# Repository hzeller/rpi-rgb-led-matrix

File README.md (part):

Controlling RGB LED display with Raspberry Pi GPIO
==================================================

A library to control commonly available 128x64, 64x64, 32x32 or 16x32 RGB LED panels
with the Raspberry Pi. Can support PWM up to 11Bit per channel, providing
true 24bpp color with CIE1931 profile.

Supports 3 chains with many panels each on a regular Pi.
On a Raspberry Pi 2 or 3, you can easily chain 12 panels in that chain
(so 36 panels total), but you can theoretically stretch that to up
to 96-ish panels (32 chain length) and still reach
around 100Hz refresh rate with full 24Bit color (theoretical - never tested
this; there might likely be timing problems with the panels that will creep
up then).

With fewer colors or so-called 'outdoor panels' you can control even more,
faster.

The LED-matrix library is (c) Henner Zeller <h.zeller@acm.org>, licensed with
[GNU General Public License Version 2.0 (or any later version)](http://www.gnu.org/licenses/gpl-2.0.txt)
(which means, if you use it in a product somewhere, you need to make the
source and all your modifications available to the receiver of such product so
that they have the freedom to adapt and improve).
Yes, you are also allowed to use
this code under the [GNU General Public License Version 3.0](http://www.gnu.org/licenses/gpl-3.0.txt)
which allows linking with Apache 2.0 code and LGPL-3.0 code.

## Discourse discussion group

**If you'd like help, please do not file a bug, use the discussion board instead:**
https://rpi-rgb-led-matrix.discourse.group/  (obviously please read this whole page first).
If you file a bug asking for personal help instead of using the discourse group, please
state in your bug that you have read this entire page and that you're indeed filing a bug
or request for improvement. Otherwise, please use the discourse group.

Overview
--------
The RGB LED matrix panels can be scored at [Sparkfun][sparkfun],
[AdaFruit][ada] or eBay and Aliexpress. If you are in China, I'd try to get
them directly from some manufacturer, Taobao or Alibaba.

The `RGBMatrix` class provided in `include/led-matrix.h` does what is needed
to control these. You can use this as a library in your own projects or just
use the demo binary provided here which provides some useful examples.

Check out [utils/ directory for some ready-made tools](./utils) to get started
using the library, or the [examples-api-use/](./examples-api-use) directory if
you want to get started programming your own utils.

Panels supported
----------------
This library does not support PWM panels (which actually are better, but need
a completely different driver).\
It should support most other panels with direct addressing (3 to 5 address lines,
ABC for 8x2=16 lines, ABCD for 16x2=32 lines, and ABCDE for 32x2=64 lines).
It also supports panels using shift registers for line addressing, also called ABC
panels up to 64 lines.\
However some amount of panels have uncommon pixel layouts, especially the brighter
panels and may require special pixel mappers (some are called zigzag or zagzig, see
https://rpi-rgb-led-matrix.discourse.group/t/p10rgb-3535-4s-zaggiz-1-4scan-abc-p10-panels-and-https-github-com-2dom-pxmatrix/921 )

Until this wiki has its own confirmed list of working panels, you can refer to
this list: https://github.com/board707/DMD_STM32/wiki/Led_drivers and assume
that all supported panels there should work with this library, or could work
with minimal work to create a pixel mapper.
Please do refer to --led-multiplexing=<0..17> mentioned below and try all values. \
2025/11 update: DMD_STM32 has started adding experimental support for some PWM panels.
These should be labelled as "special" in the table above. They are not supported by this
lib, as it only supports non PWM panels (until someone contributes PWM support).

PWM/E-PWM/S-PWM Panels
----------------------
Newer PWM panels are not currently supported by this lib, but support would really be appreciated.
- https://github.com/hzeller/rpi-rgb-led-matrix/issues/466 - Master bug tracking PWM efforts
- https://github.com/hzeller/rpi-rgb-led-matrix/issues/1866 - Continued discussion

Some experimentation and success has been made with the following fork. Some panel support with FM6373, FM6363, SM16380SH
- https://github.com/kingdo9/rpi-rgb-led-matrix_pwm_experiment

Raspberry Pi 1-5 supported
------------------------------
This library supports the old Raspberry Pi's Version 1 with 26 pin header and
also the B+ models, the Pi Zero, Raspberry Pi 2,3,4 and 5 with 40 pins, as well
as the Compute Modules which have 44 GPIOs.

#### Raspberry Pi 5 support has now been added.
There are two modes to run this on the Pi 5 

**--led-rp1-rio=0** - Uses the Pi 5 coprocessor RP1 to perform the work (default) - Very minimal CPU usage

**--led-rp1-rio=1** - Uses Registered IO block of RP1 to communicate with the GPIO - Higher CPU usage but much faster performance.\
**NOTE: --led-slowdown-gpio** can have the opposite effect in this mode, so going from 2 to 3 may increase performance slightly with --led-rp1-rio=1.

Pi 5 Discussion -  https://github.com/hzeller/rpi-rgb-led-matrix/issues/1603

Thanks to contributions from the following libraries to help implement this.
https://github.com/adafruit/Adafruit_Blinka_Raspberry_Pi5_Piomatter \
https://github.com/bitslip6/rpi-gpu-hub75-matrix \
https://www.i-programmer.info/programming/148-hardware/16887-raspberry-pi-iot-in-c-pi-5-memory-mapped-gpio.html

The 26 pin models can drive one chain of RGB panels, the 40 pin models
**up to three** chains in parallel (each chain 12 or more panels long).
The Compute Module can drive **up to 6 chains in parallel**.
The Raspberry Pi 2 and 3 are faster and generally preferred to the older
models (and the Pi Zero). With the faster models, the panels sometimes
can't keep up with the speed; check out
this [troubleshooting section](#troubleshooting) what to do.

A lightweight, non-GUI, distribution such as [DietPi] is recommended.
[Raspbian Lite][raspbian-lite] is a bit easier to get started with and
is a good second choice.

Types of Displays
-----------------
There are various types of displays that come all with the same Hub75 connector.
They vary in the way the multiplexing is happening so this library supports
options to choose that.
All these are configured by flags (or, programmatically, in an [Options struct](include/led-matrix.h#L57)).

If you have a 64x32 display, you need to supply the flags
`--led-cols=64 --led-rows=32` for instance.

Depending on the Matrix, there are various configuration options that
you might need to set for it to work. See further below in the README for the
[detailed description of these](#changing-parameters-via-command-line-flags).
While the `--led-rows` and `--led-cols` can be derived from simply looking
at the panels, the other options might require some experimenting to find the
right setting if there is no description provided by the manufacturer of
the panel. Going through these options for experiments would typically not do
harm, so you're free to experiment to find your setting.

Flag                                | Description
:---------------      | :-----------------
`--led-cols`          | Columns in the LED matrix, the 'width'.
`--led-rows`          | Rows in the LED matrix, the 'height'.
`--led-multiplexing`  | In particular bright outdoor panels with small multiplex ratios require this. Often an indicator: if there are fewer address lines than expected: ABC (instead of ABCD) for 32 high panels and ABCD (instead of ABCDE) for 64 high panels.
`--led-row-addr-type` | Addressing of rows; in particular panels with only AB address lines might indicate that this is needed.
`--led-panel-type`    | Chipset of the panel. In particular if it doesn't light up at all, you might need to play with this option because it indicates that the panel requires a particular initialization sequence.

Panels can be chained by connecting the output of one panel to the input of
the next panel. You can chain quite a few together, but the refresh rate will
reduce with longer chains.

The 64x64 matrixes typically come in two kinds: with 5 address
lines (A, B, C, D, E), or (A, B); the latter needs a `--led-row-addr-type=1`
parameter. So-called 'outdoor panels' are typically brighter and allow for
faster refresh-rate for the same size, but do some multiplexing internally
of which there are a few types out there; they can be chosen with
the `--led-multiplexing` parameter.
Many 128x64 panels now use ABC addressing using shift registers, instead of direct
ABCDE addressing. Look at using --led-row-addr-type=5 or --led-row-addr-type=3
with them (and you may need to use --led-slowdown-gpio of 2 or more. Please
see this bug for more details: https://github.com/hzeller/rpi-rgb-led-matrix/issues/1774

There are some panels that have a different chip-set than the default HUB75.
These require some initialization sequence. The current supported types are
`--led-panel-type=FM6126A` and `--led-panel-type=FM6127`.

Generally, the higher scan-rate (e.g. 1:8), a.k.a. outdoor panels generally
allow faster refresh rate, but you might need to figure out the multiplexing
mapping if one of the three provided does not work.

Some 32x16 outdoor matrixes with 1:4 scan (e.g. [Qiangli Q10(1/4) or X10(1/4)](http://qiangliled.com/products-63.html))
have 4 address line (A, B, C, D). For such matrices is necessary to
use `--led-row-addr-type=2` parameter. Also the matrix Qiangli Q10(1/4)
have "Z"-stripe pixel mapping and in this case, you'd use two parameters
at the same time `--led-row-addr-type=2 --led-multiplexing=4`.

Sub-Pages
---------
This documentation is split into parts that help you through the process

- 
    [**Wire up the matrix to your Pi**](./wiring.md). This document describes
    what goes where.
- [How to map pixels between panels or within panels](./lib). This is crucial for figuring out pixel mappers,
  matrix mappers and so forth. This is where you will learn about panel layout with U-Mapper, V-Mapper, V-Mapper:Z
- [Adapter GPIO boards output to up to 3 channels (electrodragon board recommended)](./adapter).
    If you have an [Adafruit HAT] or [Adafruit Bonnet], you can choose that with
    a command line option [described below](#if-you-have-an-adafruit-hat-or-bonnet)
- [All the command line options you can give to demo and in turn use in your library code](./examples-api-use).
- [Installing an Optimized Kernel to fix most flickering issues](./optimized-kernel)

Python Support
--------------
The python bindings have been overhauled as of February 2026 and are now built with scikit-build-core and cmake. While
this update has been tested there are likely edge cases that have not been caught. Please subscribe to the master Python
bug to assist or check for the latest updates.
https://github.com/hzeller/rpi-rgb-led-matrix/issues/1749.

The entire repository itself is PIP-able and can be installed as a package directly. Python dev packages are required.
```
sudo apt-get install python-dev-is-python3 python3-pil cython3
pip install git+https://github.com/hzeller/rpi-rgb-led-matrix
```

Rpi Hardware Support
--------------------
While this code should still work on rPi1 or Rpi0, those are underpowered and not recommended. An ESP32 is cheaper and faster.
Rpi2 is honestly old and slow too.
Rpi3 / Rpi3a / Rpi0 2wl will work for most displays but will be slow if you are rotating a huge display in a mapper (Rpi0 2wl is a slightly faster version of Rpi3)
Rpi4 is the fastest supported chip which will need a higher slowdown gpio value to avoid overwhelming panels (if they display garbage)
Rpi5 is not officially supported as of 2025/11, but see https://github.com/hzeller/rpi-rgb-led-matrix/issues/1603

Let's do it
------------
  1. Run a demo. You find that in the
     [examples-api-use/](./examples-api-use#running-some-demos) directory:
```
make -C examples-api-use
sudo examples-api-use/demo -D0
```
  2. Use the utilities. The [utils](./utils) directory has some ready-made
    useful utilities to show content. [Go there](./utils) to see how to
    compile and run these.
  3. Write your own programs using the Matrix in C++ or one of the
     bindings such as Python or C#.

### Wiring / Boards

Please see the [Adadpter Boards or Self Wiring](./adapter).

Summary is:
- Yes you can self wire without level shifters and it will work most of the time, but if you're not in a hurry get a board
- https://www.electrodragon.com/product/rgb-matrix-panel-drive-board-for-raspberry-pi-v2/ **is the recommended solution with 3 channels and level shifters**. You can't go wrong there, but expect a bit of shipping time.
- If shipping time is crucial and you don't want to wire your own, Adafruit sells a single channel board (the electrodragon one is 3 channels), but note that its wiring is non standard and requires a special compile option or command line argument: https://www.adafruit.com/product/3211

### Utilities

The [utils directory](./utils) is meant for ready utilities to show images or
animated gifs or videos. Read the [README](./utils/README.md) there for
instructions how to compile.

There are external projects that use this library and provide higher level
network protocols, such as the
 * [FlaschenTaschen implementation](https://github.com/hzeller/flaschen-taschen)
   (VLC can send videos to it natively)
 * [PixelPusher implementation](https://github.com/hzeller/rpi-matrix-pixelpusher) (common in light art installations)
 * [ZeroMQ-server](https://github.com/Knifa/led-matrix-zmq-server) to receive
   content.
 * Marc's [FastLED_RPIRGBPanel_GFX](http://marc.merlins.org/perso/arduino/post_2020-01-01_Running-FastLED_-Adafruit_GFX_-and-LEDMatrix-code-on-High-Resolution-RGBPanels-with-a-Raspberry-Pi.html) allows running arduino code on linux/rPi and display on bigger RGBPanel matrices than arduino chips, can.

### API

The library comes as an API that you can use for your own utilities and use-cases.

  * The native library is a C++ library (see [include/](./include)).
    Example uses you find in the [examples-api-use/](./examples-api-use)
    directory.
  * If you prefer to program in C, there is also a
    [C API](./include/led-matrix-c.h).
  * In the [python](./bindings/python) subdirectory, you find a Python API including a
    couple of [examples](./bindings/python/samples) to get started.
  * There are a couple of external bindings, such as
      * [Nodejs binding] by Maxime Journaux
      * [Nodejs/Typescript binding] by Alex Eden
      * [Go binding] by Máximo Cuadros
      * [Rust binding] by Vincent Pasquier

### Changing parameters via command-line flags

For the programs in this distribution and also automatically in your own
programs using this library, there are a lot of parameters provided as command
line flags, so that you don't have to re-compile your programs to tweak them.
Some might need to be changed for your particular kind of panel.

Here is a little run-down of what these command-line flags do and when you'd
like to change them.

First things first: if you have a different wiring than described in
[wiring](./wiring.md), for instance if you have an Adafruit HAT/Bonnet, you can
choose these here:

```
--led-gpio-mapping=<gpio-mapping>: Name of GPIO mapping used. Default "regular"
```

This can have values such as
  - `--led-gpio-mapping=regular` The standard mapping of this library, described in the [wiring](./wiring.md) page.
  - `--led-gpio-mapping=adafruit-hat` The Adafruit HAT/Bonnet, that uses this library or
  - `--led-gpio-mapping=adafruit-hat-pwm` Adafruit HAT with the anti- hardware mod [described below](#improving-flicker-hardware-patch).
  - `--led-gpio-mapping=compute-module` Additional 3 parallel chains can be used with the Compute Module.

Learn more about the mappings in the [wiring documentation](wiring.md#alternative-hardware-mappings).

#### GPIO speed

```
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
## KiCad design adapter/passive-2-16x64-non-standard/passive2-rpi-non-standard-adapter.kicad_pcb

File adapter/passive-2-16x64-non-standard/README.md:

Adapter PCB to support up to 2 panel chains
===========================================

   * This adapter is designed specifically for 16x64 LED matrix boards that use a non standard pin layout
 
   * This is a passive board. It is simple, but the logic level will be out of
     spec for the LED matrix (3.3V vs. 5V) which might or might not work.
     Driving long cables with the GPIO pins is also not a good idea.
   * Only really advisable, if the LED panels have 74HCT245 (as opposed to just
     74HC245) in their input stage, because then they can deal properly with
     the 3.3V logic levels coming from the Pi.
   * Open source KiCAD PCB EDA format.
   * autorouted 
   * The FAB files are provided as [passive2-rpi-non-standard-adapter-fab.zip](./passive2-rpi-non-standard-adapter-fab.zip)

This board is [shared on OSH Park][osh-passive3] (not affiliated).

![Preview][rendering]

[rendering]: ../../img/passive2-rpi-non-standard-adapter.png

[osh-passive3]: https://oshpark.com/shared_projects/LxM7tyyO

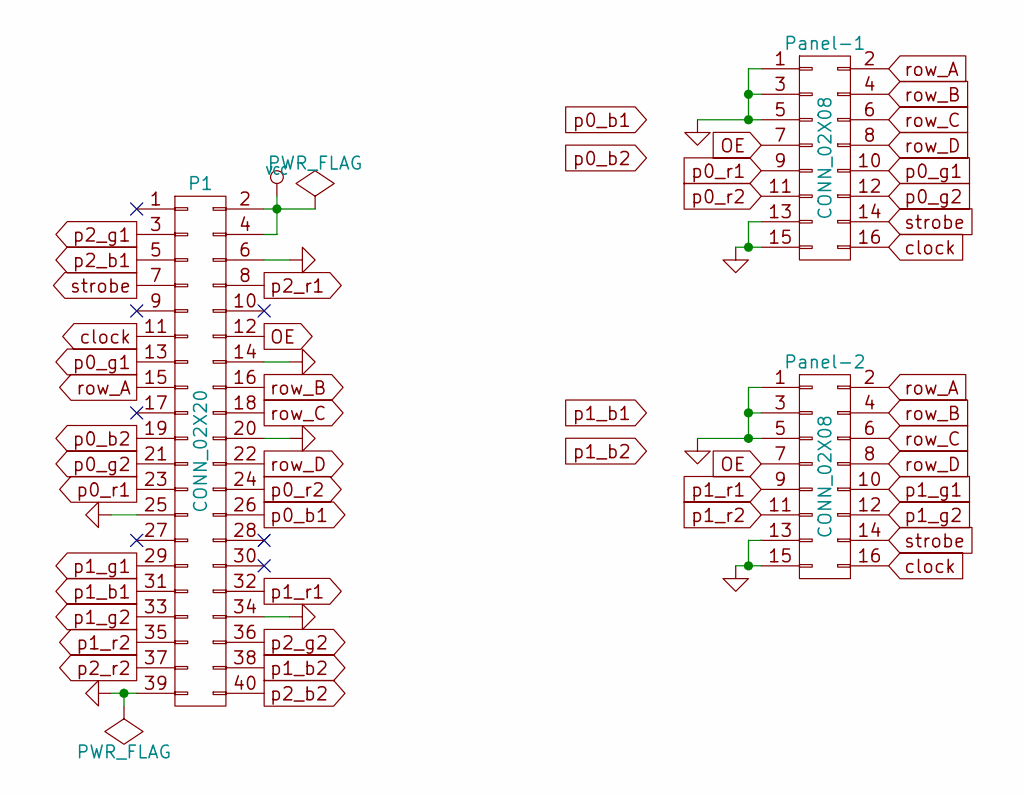
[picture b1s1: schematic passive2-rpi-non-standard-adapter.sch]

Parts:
P1: CONN_02X20; Pin_Header_Straight_2x20
Panel-1, Panel-2: CONN_02X08; Pin_Header_Straight_2x08

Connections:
GND: P1.6, P1.14, P1.20, P1.25, P1.34, P1.39, Panel-1.1, Panel-1.3, Panel-1.5, Panel-1.13, Panel-1.15, Panel-2.1, Panel-2.3, Panel-2.5, Panel-2.13, Panel-2.15
OE: P1.12, Panel-1.7, Panel-2.7
VCC: P1.2, P1.4
clock: P1.11, Panel-1.16, Panel-2.16
p0_b1: P1.26
p0_b2: P1.19
p0_g1: P1.13, Panel-1.10
p0_g2: P1.21, Panel-1.12
p0_r1: P1.23, Panel-1.9
p0_r2: P1.24, Panel-1.11
p1_b1: P1.31
p1_b2: P1.38
p1_g1: P1.29, Panel-2.10
p1_g2: P1.33, Panel-2.12
p1_r1: P1.32, Panel-2.9
p1_r2: P1.35, Panel-2.11
p2_b1: P1.5
p2_b2: P1.40
p2_g1: P1.3
p2_g2: P1.36
p2_r1: P1.8
p2_r2: P1.37
row_A: P1.15, Panel-1.2, Panel-2.2
row_B: P1.16, Panel-1.4, Panel-2.4
row_C: P1.18, Panel-1.6, Panel-2.6
row_D: P1.22, Panel-1.8, Panel-2.8
strobe: P1.7, Panel-1.14, Panel-2.14

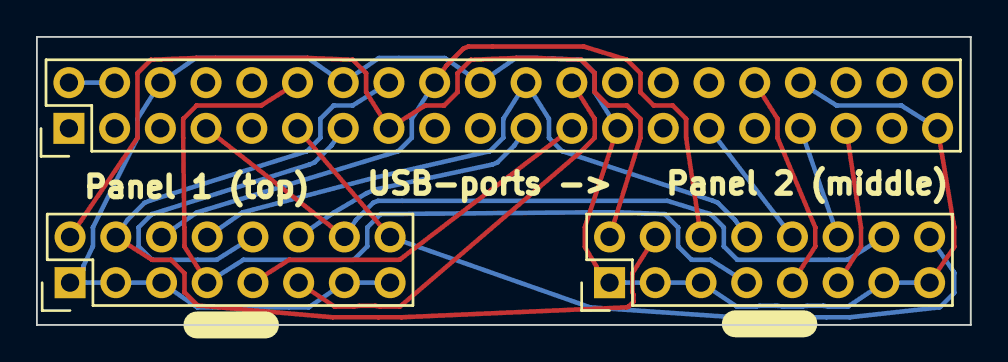
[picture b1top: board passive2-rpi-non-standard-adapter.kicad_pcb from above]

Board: 2 copper layers, 51.9 x 16.0 mm, 3 parts (0 on the bottom side), 17 nets.

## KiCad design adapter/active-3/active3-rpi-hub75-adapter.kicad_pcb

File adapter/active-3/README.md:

Adapter PCB to support up to 3 panel chains
===========================================

   * Supports up to three panel chains for newer plus models and
     Raspberry Pi 2 that have 40 GPIO pins.
   * Uses HCT245 to level shift signals from 3.3V to 5V and shield
     the Raspberry Pi GPIOs from overloading.
   * Open source KiCAD PCB EDA format.
   * Optional: Pads to power the Pi with 5V, including optional capacitor footprints.
   * Connector for RxD input (literally the only GPIO pin left) in case you want to
     make your panel controlled with a serial interface (3.3V logic level).
   * Provides a way to choose the pinout for different kinds of 64x64 matrixes.
   * (not very pretty layout, was just lazy and let the auto-router generate the first pass)
   * BOM:
     - 4x 74HCT245 or 74AHCT245 in 20-SOIC, 7.5mm package which should make
     it easy to hand-solder. Make sure to get the variant with the **T**: HC**T** or AHC**T**
     (there are also HC or AHC, don't use these).
     - 4x 100nF ceramic capacitor (0805 package)
     - 1x 10kOhm resistor (0805 package). Not critical, just a pullup (2.2k .. 15k probably ok).
     - 3x 16pin IDC (=2x8) male receptible to connect the panels.
     - 1x 40pin female connector to connect to the RPi.
     - 1x (optional) 22μF .. 100μF capacitor for 5V rail (either 1206 SMD or
       radial electrolytic with 2.5mm pitch/6.3mm diameter)
   * The Gerber FAB files are provided as [active3-rpi-hub75-adapter-fab.zip](./active3-rpi-hub75-adapter-fab.zip)

The board is also [shared on OSH Park][osh-active3] (not affiliated).

![Preview][rendering]
![Real World][real-world]

Essentially, this is connecting the output pins through level shifting buffers (they
are operated at 5V, but the HCT series chips accept 3.3V input levels from the Pi). The
strobe, OE and clock signals are separately buffered for each connector.

![Schematic][schematic]

## Optional

### Power in

The area on the left has 5V/GND input pads, that allow you to power your Raspberry Pi from
a 5V source ... which you are likely to have as you are powering the LED Matrix. This is often
more convenient than using the USB connector to power the Pi.

If you do that, there are pads to add a capacitor to smooth the supply - two footprints are
provided: C5 and C6 for through-hole or surface mount components. The value is not critical;
I usually use a 22μF/6.3V ceramic capacitor on the C6 pads.

### Choose E-Line for 64x64 panels with 1:32 multiplexing

If you have a 64x64 matrix with 1:32 multiplexing, you need to supply an `E`-address line to it.
While the Address lines `A` to `D` have fixed positions on the Hub75 connector, there
seem to be two different ways to connect the `E` address line: it is either on pin 4 or pin 8
of the connector. So this adapter board provides the flexibility to choose the right pin for
your matrix.

Look at the back of the matrix or the documentation to find out for your specific board where
to connect E.

Once you know that, the jumper area in the bottom left of this adapter board allows to choose
to which pin to connect the E-address line to. The corresponding other pin should be connected
to GND. Simply solder a wire bridge as indicated below (or use a jumper that you can change later).

If you are not using such 64x64 matrix, you can connect both these pins to GND.

Here are the typical configurations:

No 1:32 64x64: to GND    | E-Line on Pin 4   | E-Line on Pin 8|
-------------------------|-------------------|----------------
![][config-default]      |![][config-pin4]   |![][config-pin8]

### Input for serial RxD

If you are not using a 64x64 display that occupies the E-Line, you can use the RxD serial input -
this might come in handy if you are using the display to be controlled by a serial line. Be aware
that the input requires 3.3V level, so if you have a RS232, make sure to first adapt the levels.

[rendering]: ../../img/active3-pcb.png
[config-default]: ../../img/active3-pcb-config-default.png
[config-pin4]: ../../img/active3-pcb-config-pin4.png
[config-pin8]: ../../img/active3-pcb-config-pin8.png
[schematic]: ../../img/active3-schematic.png
[real-world]: ../../img/three-parallel-panels-soic.jpg
[osh-active3]: https://oshpark.com/shared_projects/6xAD1VXr

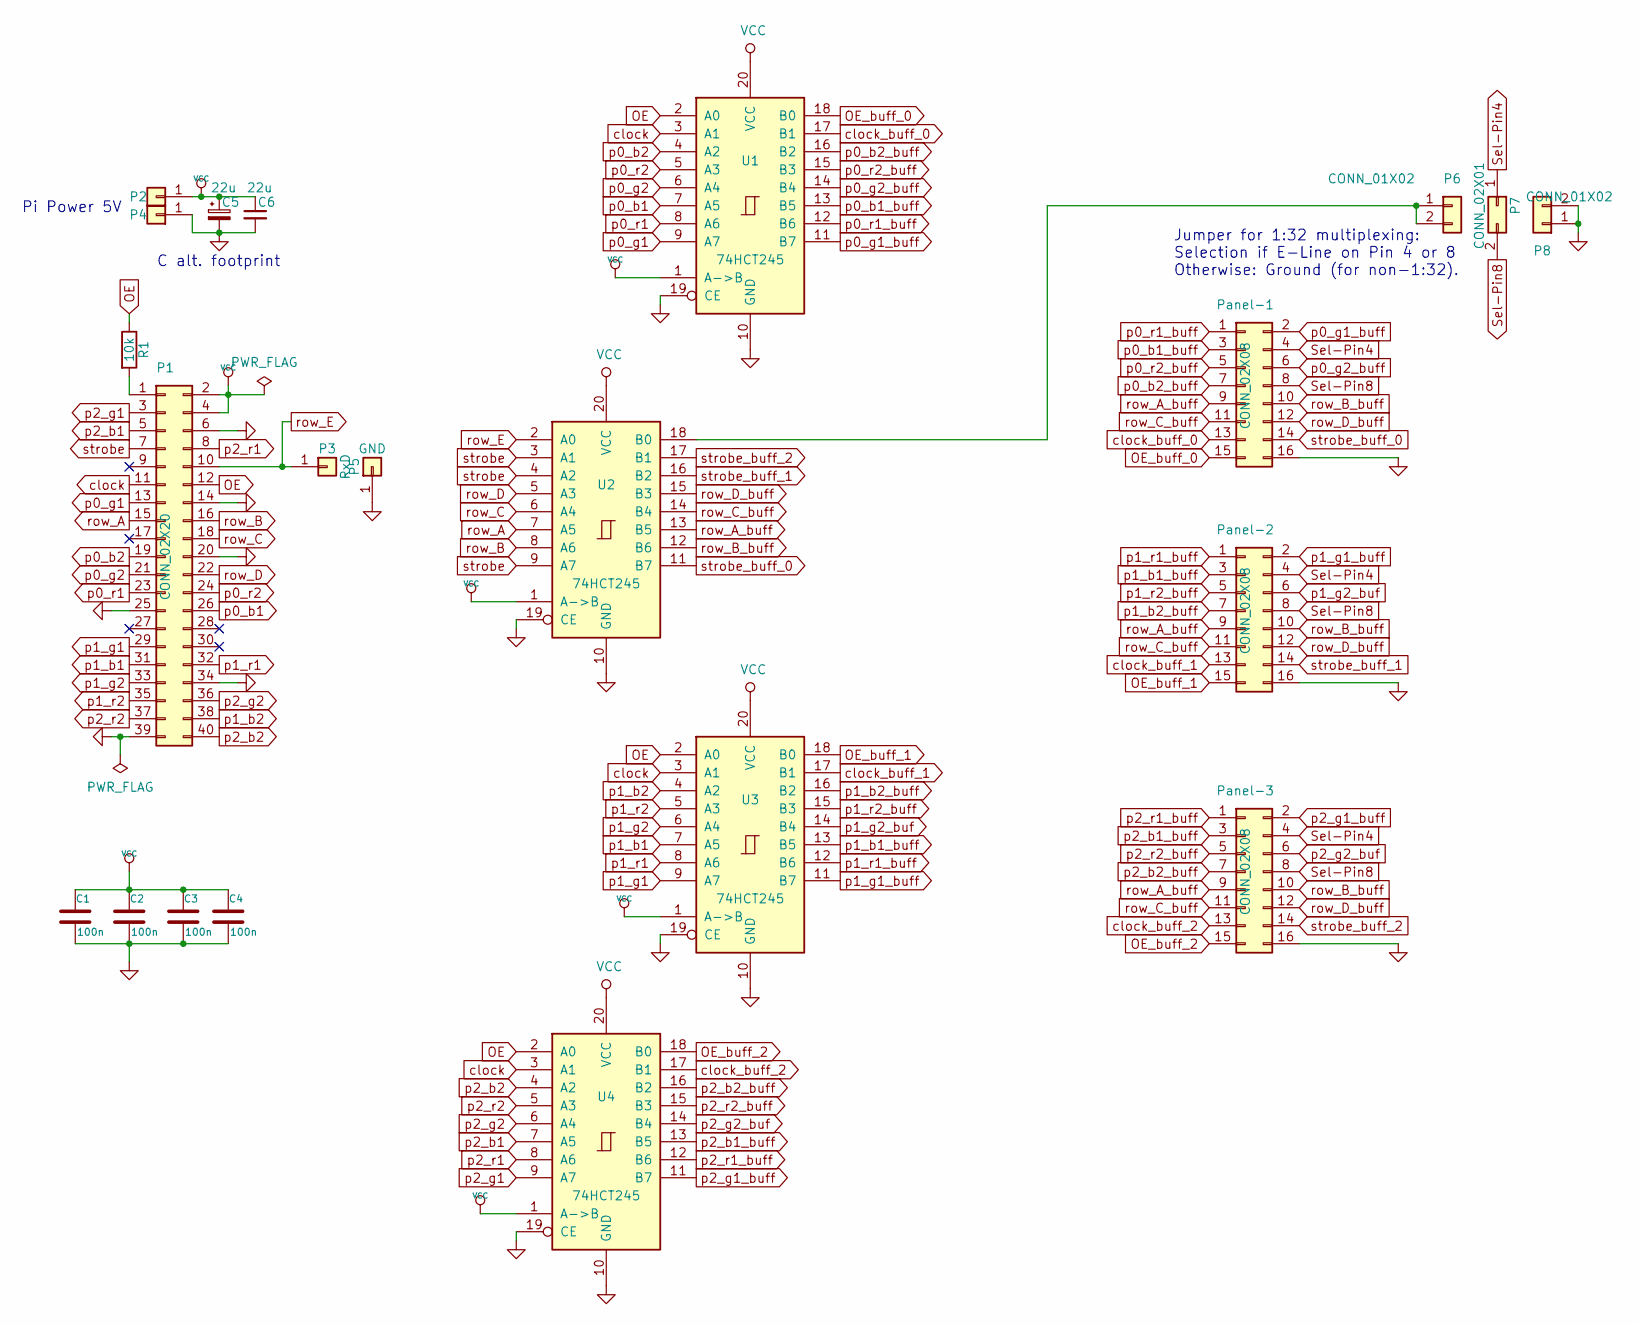
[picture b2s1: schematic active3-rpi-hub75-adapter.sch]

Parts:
C1, C2, C3, C4: 100n; C_0805_2012Metric
C5: 22u; CP_Radial_D6.3mm_P2.50mm
C6: 22u; C_1206_3216Metric
P1: CONN_02X20; Pin_Header_Straight_2x20
P2: +5V; Pin_Header_Straight_1x01
P3: RxD; Pin_Header_Straight_1x01
P4, P5: GND; Pin_Header_Straight_1x01
P6, P8: CONN_01X02; Pin_Header_Straight_1x02
P7: CONN_02X01; Pin_Header_Straight_1x02
Panel-1, Panel-2, Panel-3: CONN_02X08; IDC-Header_2x08_P2.54mm_Vertical
R1: 10k; R_0805_2012Metric
U1, U2, U3, U4: 74HCT245; SOIC-20W_7.5x12.8mm_P1.27mm

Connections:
GND: C1.2, C2.2, C3.2, C4.2, C5.2, C6.2, P1.6, P1.14, P1.20, P1.25, P1.34, P1.39, P4.1, P5.1, P8.1, P8.2, Panel-1.16, Panel-2.16, Panel-3.16, U1.10 (GND), U1.19 (CE), U2.10 (GND), U2.19 (CE), U3.10 (GND), U3.19 (CE), U4.10 (GND), U4.19 (CE)
unnamed: P1.1, R1.2
unnamed: P6.1, P6.2, U2.18 (B0)
OE: P1.12, R1.1, U1.2 (A0), U3.2 (A0), U4.2 (A0)
OE_buff_0: Panel-1.15, U1.18 (B0)
OE_buff_1: Panel-2.15, U3.18 (B0)
OE_buff_2: Panel-3.15, U4.18 (B0)
Sel-Pin4: P7.1, Panel-1.4, Panel-2.4, Panel-3.4
Sel-Pin8: P7.2, Panel-1.8, Panel-2.8, Panel-3.8
VCC: C1.1, C2.1, C3.1, C4.1, C5.1, C6.1, P1.2, P1.4, P2.1, U1.1 (A->B), U1.20 (VCC), U2.1 (A->B), U2.20 (VCC), U3.1 (A->B), U3.20 (VCC), U4.1 (A->B), U4.20 (VCC)
clock: P1.11, U1.3 (A1), U3.3 (A1), U4.3 (A1)
clock_buff_0: Panel-1.13, U1.17 (B1)
clock_buff_1: Panel-2.13, U3.17 (B1)
clock_buff_2: Panel-3.13, U4.17 (B1)
p0_b1: P1.26, U1.7 (A5)
p0_b1_buff: Panel-1.3, U1.13 (B5)
p0_b2: P1.19, U1.4 (A2)
p0_b2_buff: Panel-1.7, U1.16 (B2)
p0_g1: P1.13, U1.9 (A7)
p0_g1_buff: Panel-1.2, U1.11 (B7)
p0_g2: P1.21, U1.6 (A4)
p0_g2_buff: Panel-1.6, U1.14 (B4)
p0_r1: P1.23, U1.8 (A6)
p0_r1_buff: Panel-1.1, U1.12 (B6)
p0_r2: P1.24, U1.5 (A3)
p0_r2_buff: Panel-1.5, U1.15 (B3)
p1_b1: P1.31, U3.7 (A5)
p1_b1_buff: Panel-2.3, U3.13 (B5)
p1_b2: P1.38, U3.4 (A2)
p1_b2_buff: Panel-2.7, U3.16 (B2)
p1_g1: P1.29, U3.9 (A7)
p1_g1_buff: Panel-2.2, U3.11 (B7)
p1_g2: P1.33, U3.6 (A4)
p1_g2_buf: Panel-2.6, U3.14 (B4)
p1_r1: P1.32, U3.8 (A6)
p1_r1_buff: Panel-2.1, U3.12 (B6)
p1_r2: P1.35, U3.5 (A3)
p1_r2_buff: Panel-2.5, U3.15 (B3)
p2_b1: P1.5, U4.7 (A5)
p2_b1_buff: Panel-3.3, U4.13 (B5)
p2_b2: P1.40, U4.4 (A2)
p2_b2_buff: Panel-3.7, U4.16 (B2)
p2_g1: P1.3, U4.9 (A7)
p2_g1_buff: Panel-3.2, U4.11 (B7)
p2_g2: P1.36, U4.6 (A4)
p2_g2_buf: Panel-3.6, U4.14 (B4)
p2_r1: P1.8, U4.8 (A6)
p2_r1_buff: Panel-3.1, U4.12 (B6)
p2_r2: P1.37, U4.5 (A3)
p2_r2_buff: Panel-3.5, U4.15 (B3)
row_A: P1.15, U2.7 (A5)
row_A_buff: Panel-1.9, Panel-2.9, Panel-3.9, U2.13 (B5)
row_B: P1.16, U2.8 (A6)
row_B_buff: Panel-1.10, Panel-2.10, Panel-3.10, U2.12 (B6)
row_C: P1.18, U2.6 (A4)
row_C_buff: Panel-1.11, Panel-2.11, Panel-3.11, U2.14 (B4)
row_D: P1.22, U2.5 (A3)
row_D_buff: Panel-1.12, Panel-2.12, Panel-3.12, U2.15 (B3)
row_E: P1.10, P3.1, U2.2 (A0)
strobe: P1.7, U2.3 (A1), U2.4 (A2), U2.9 (A7)
strobe_buff_0: Panel-1.14, U2.11 (B7)
strobe_buff_1: Panel-2.14, U2.16 (B2)
strobe_buff_2: Panel-3.14, U2.17 (B1)

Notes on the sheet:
Pi Power 5V
C alt. footprint
Jumper for 1:32 multiplexing: Selection if E-Line on Pin 4 or 8 Otherwise: Ground (for non-1:32).

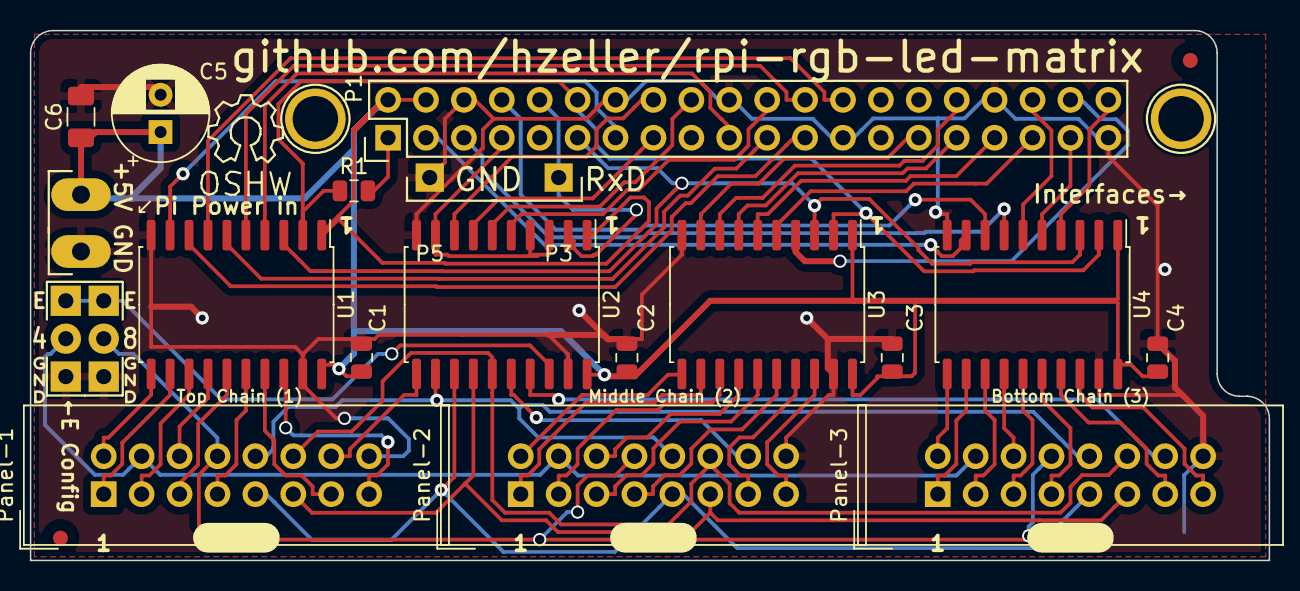
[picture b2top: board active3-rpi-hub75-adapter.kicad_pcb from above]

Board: 2 copper layers, 83.0 x 35.5 mm, 24 parts (0 on the bottom side), 63 nets.

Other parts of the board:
P20, P21: CONN_01X01; 1pin

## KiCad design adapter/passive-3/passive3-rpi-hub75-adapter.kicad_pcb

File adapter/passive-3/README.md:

Adapter PCB to support up to 3 panel chains
===========================================

   * This is a passive board. It is simple, but the logic level will be out of
     spec for the LED matrix (3.3V vs. 5V) which might or might not work.
     Driving long cables with the GPIO pins is also not a good idea.
   * You typically want to consider using the [active board](../active-3).
   * Works for Matrix up to 1:16 multiplexing (32 rows). For 1:32 multiplexing,
     you want to use the [active board](../active-3). You can of also hack
     this board as [suggested in this bugtracker entry](https://github.com/hzeller/rpi-rgb-led-matrix/issues/360#issuecomment-321104348) to make it work with
     64x64 boards.
   * Only really advisable, if the LED panels have 74HCT245 (as opposed to just
     74HC245) in their input stage, because then they can deal properly with
     the 3.3V logic levels coming from the Pi.
   * Supports up to three panel chains for newer plus models and
     Raspberry Pi 2/3 that have 40 GPIO pins.
   * Open source KiCAD PCB EDA format.
   * (not very pretty layout, was just lazy and let the auto-router do it).
   * The FAB files are provided as [passive3-rpi-hub75-adapter-fab.zip](./passive3-rpi-hub75-adapter-fab.zip)

This board is [shared on OSH Park][osh-passive3] (not affiliated).

![Preview][rendering]

[rendering]: ../../img/passive3-pcb.png
[osh-passive3]: https://oshpark.com/shared_projects/FNAtZUsP

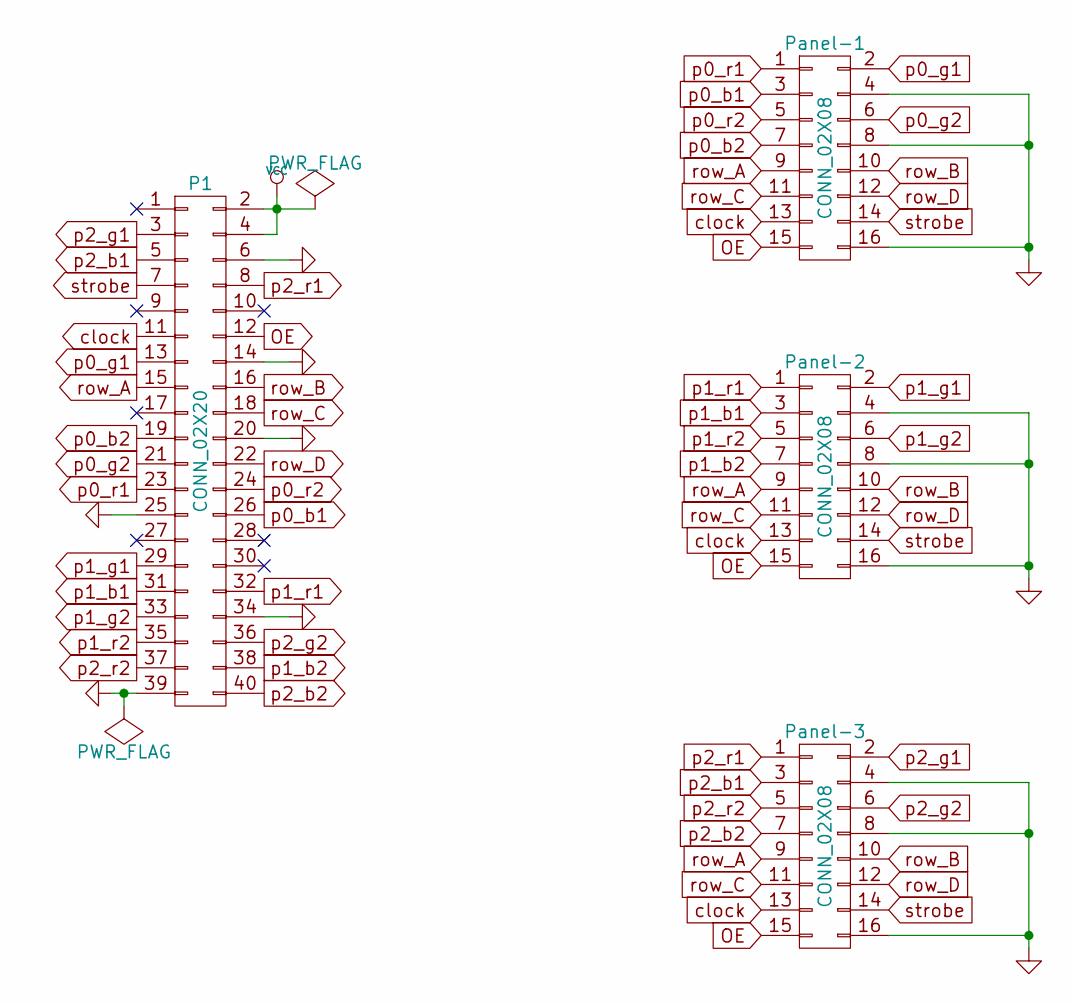
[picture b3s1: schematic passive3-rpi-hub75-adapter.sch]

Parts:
P1: CONN_02X20; Pin_Header_Straight_2x20
Panel-1, Panel-2, Panel-3: CONN_02X08; Pin_Header_Straight_2x08

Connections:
GND: P1.6, P1.14, P1.20, P1.25, P1.34, P1.39, Panel-1.4, Panel-1.8, Panel-1.16, Panel-2.4, Panel-2.8, Panel-2.16, Panel-3.4, Panel-3.8, Panel-3.16
OE: P1.12, Panel-1.15, Panel-2.15, Panel-3.15
VCC: P1.2, P1.4
clock: P1.11, Panel-1.13, Panel-2.13, Panel-3.13
p0_b1: P1.26, Panel-1.3
p0_b2: P1.19, Panel-1.7
p0_g1: P1.13, Panel-1.2
p0_g2: P1.21, Panel-1.6
p0_r1: P1.23, Panel-1.1
p0_r2: P1.24, Panel-1.5
p1_b1: P1.31, Panel-2.3
p1_b2: P1.38, Panel-2.7
p1_g1: P1.29, Panel-2.2
p1_g2: P1.33, Panel-2.6
p1_r1: P1.32, Panel-2.1
p1_r2: P1.35, Panel-2.5
p2_b1: P1.5, Panel-3.3
p2_b2: P1.40, Panel-3.7
p2_g1: P1.3, Panel-3.2
p2_g2: P1.36, Panel-3.6
p2_r1: P1.8, Panel-3.1
p2_r2: P1.37, Panel-3.5
row_A: P1.15, Panel-1.9, Panel-2.9, Panel-3.9
row_B: P1.16, Panel-1.10, Panel-2.10, Panel-3.10
row_C: P1.18, Panel-1.11, Panel-2.11, Panel-3.11
row_D: P1.22, Panel-1.12, Panel-2.12, Panel-3.12
strobe: P1.7, Panel-1.14, Panel-2.14, Panel-3.14

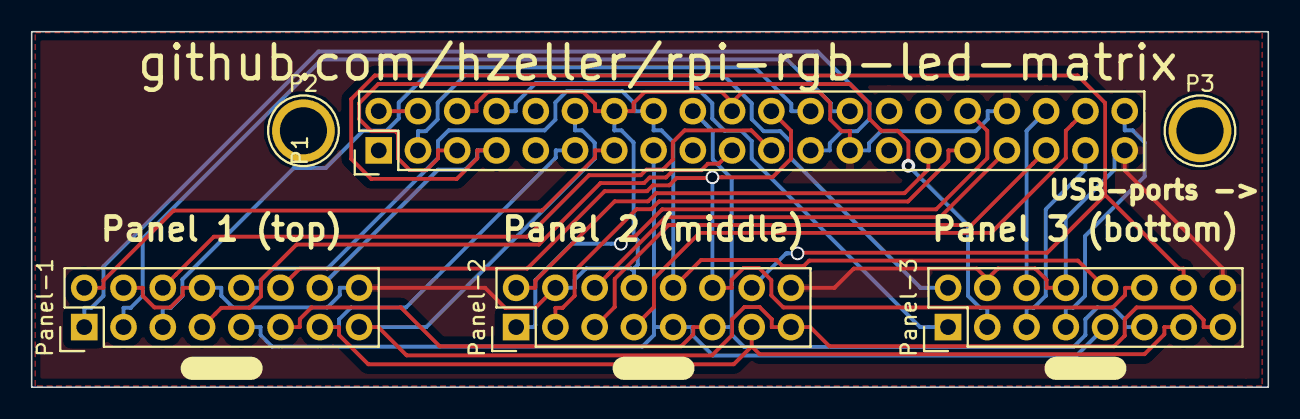
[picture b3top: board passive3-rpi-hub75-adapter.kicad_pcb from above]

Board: 2 copper layers, 80.0 x 23.0 mm, 6 parts (0 on the bottom side), 27 nets.

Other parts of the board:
P2, P3: CONN_01X01; 1pin

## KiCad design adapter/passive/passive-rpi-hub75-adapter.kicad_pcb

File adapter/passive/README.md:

Passive Adapter PCB to support up to 2 panels
=============================================

   * Supports one panel for Raspberry PIs with 26 GPIO pins and two
     panels for newer plus models and Raspberry Pi 2 that have 40 GPIO pins.
   * This board is passive, so it does not need any more components than the
     connectors. If you have trouble with erratic pixels or need to connect
     long cables, then level shifting and buffering might help; check out
     the active boards in this case.
   * This supports two panels and provides convenient breakouts
     for I²C and the serial interface.
   * Open source KiCAD PCB EDA format.

For multiple parallel boards to work and using the I2C and serial interface you have to uncomment

     #DEFINES+=-DSUPPORT_MULTI_PARALLEL   # remove the '#' in the begging

in [lib/Makefile](../../lib/Makefile).

![Preview][rendering]

[rendering]: ../../img/passive2-pcb.png

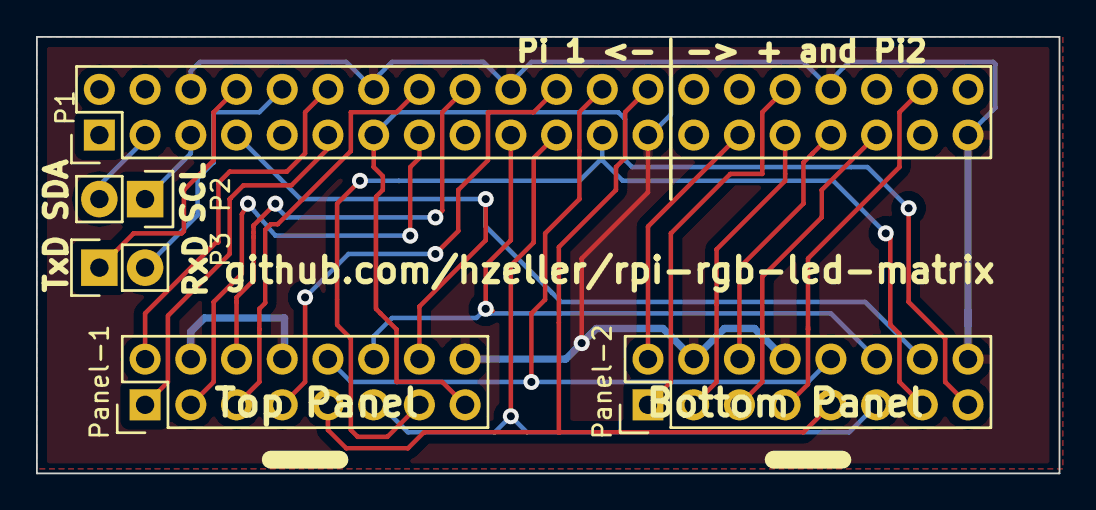
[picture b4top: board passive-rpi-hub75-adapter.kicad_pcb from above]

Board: 2 copper layers, 56.8 x 24.2 mm, 5 parts (0 on the bottom side), 25 nets.

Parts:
P1: CONN_02X20; Pin_Header_Straight_2x20
P2, P3: CONN_01X02; Pin_Header_Straight_1x02
Panel-1, Panel-2: CONN_02X08; Pin_Header_Straight_2x08

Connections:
GND: P1.6, P1.14, P1.20, P1.25, P1.34, P1.39, Panel-1.4, Panel-1.8, Panel-1.16, Panel-2.4, Panel-2.8, Panel-2.16
unnamed: P1.3, P2.2
unnamed: P1.5, P2.1
unnamed: P1.8, P3.1
unnamed: P1.10, P3.2
OE: P1.13, Panel-1.15, Panel-2.15
VCC: P1.2, P1.4
clock: P1.23, Panel-1.13, Panel-2.13
p0_b1: P1.15, Panel-1.3
p0_b2: P1.22, Panel-1.7
p0_g1: P1.12, Panel-1.2
p0_g2: P1.18, Panel-1.6
p0_r1: P1.11, Panel-1.1
p0_r2: P1.16, Panel-1.5
p1_b1: P1.31, Panel-2.3
p1_b2: P1.38, Panel-2.7
p1_g1: P1.29, Panel-2.2
p1_g2: P1.33, Panel-2.6
p1_r1: P1.32, Panel-2.1
p1_r2: P1.35, Panel-2.5
row_A: P1.26, Panel-1.9, Panel-2.9
row_B: P1.24, Panel-1.10, Panel-2.10
row_C: P1.21, Panel-1.11, Panel-2.11
row_D: P1.19, Panel-1.12, Panel-2.12
strobe: P1.7, Panel-1.14, Panel-2.14

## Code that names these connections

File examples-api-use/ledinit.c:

#include <err.h>
#include <stdint.h>
#include <stdio.h>
#include <stdlib.h>
#include <time.h>
#include <unistd.h>

#include <pigpio.h>


const uint8_t HI = 1;
const uint8_t LO = 0;
const uint8_t kReg1[] = {
    LO, HI, HI, HI, HI, HI, HI, HI,
    HI, HI, HI, HI, HI, HI, HI, HI,
};
const uint8_t kReg2[] = {
    LO, LO, LO, LO, LO, LO, LO, LO,
    LO, HI, LO, LO, LO, LO, LO, LO,
};
typedef uint32_t gpio_bits_t;  /* this should probably come from gpio.h */
struct HardwareMapping {
  const char *name;
  int max_parallel_chains;
  gpio_bits_t output_enable;
  gpio_bits_t clock;
  gpio_bits_t strobe;
  gpio_bits_t a, b, c, d, e;
  gpio_bits_t p0_r1, p0_g1, p0_b1;
  gpio_bits_t p0_r2, p0_g2, p0_b2;
  gpio_bits_t p1_r1, p1_g1, p1_b1;
  gpio_bits_t p1_r2, p1_g2, p1_b2;
  gpio_bits_t p2_r1, p2_g1, p2_b1;
  gpio_bits_t p2_r2, p2_g2, p2_b2;
};

#define GPIO_BIT(b) (b)

struct HardwareMapping hm = {
    .name          = "ji-hat",

    .output_enable = GPIO_BIT(18),
    .clock         = GPIO_BIT(27),
    .strobe        = GPIO_BIT(21),

    /* Address lines */
    .a             = GPIO_BIT(16),
    .b             = GPIO_BIT(19),
    .c             = GPIO_BIT(20),
    .d             = GPIO_BIT(26),
    .e             = GPIO_BIT(13),

    /* Parallel chain 0, RGB for both sub-panels */
    .p0_r1         = GPIO_BIT(4),
    .p0_g1         = GPIO_BIT(15),
    .p0_b1         = GPIO_BIT(14),
    .p0_r2         = GPIO_BIT(3),
    .p0_g2         = GPIO_BIT(17),
    .p0_b2         = GPIO_BIT(2),

    /* Chain 1 */
    .p1_r1         = GPIO_BIT(10),
    .p1_g1         = GPIO_BIT(25),
    .p1_b1         = GPIO_BIT(24),
    .p1_r2         = GPIO_BIT(22),
    .p1_g2         = GPIO_BIT(9),
    .p1_b2         = GPIO_BIT(23),

    /* Chain 2 */
    .p2_r1         = GPIO_BIT(5),
    .p2_g1         = GPIO_BIT(12),
    .p2_b1         = GPIO_BIT(7),
    .p2_r2         = GPIO_BIT(8),
    .p2_g2         = GPIO_BIT(6),
    .p2_b2         = GPIO_BIT(11),
};


inline void hmset(uint8_t bit) {
  gpioWrite(hm.p0_r1, bit);
  gpioWrite(hm.p0_g1, bit);
  gpioWrite(hm.p0_b1, bit);
  gpioWrite(hm.p0_r2, bit);
  gpioWrite(hm.p0_g2, bit);
  gpioWrite(hm.p0_b2, bit);
  gpioWrite(hm.p1_r1, bit);
  gpioWrite(hm.p1_g1, bit);
  gpioWrite(hm.p1_b1, bit);
  gpioWrite(hm.p1_r2, bit);
  gpioWrite(hm.p1_g2, bit);
  gpioWrite(hm.p1_b2, bit);
  gpioWrite(hm.p2_r1, bit);
  gpioWrite(hm.p2_g1, bit);
  gpioWrite(hm.p2_b1, bit);
  gpioWrite(hm.p2_r2, bit);
  gpioWrite(hm.p2_g2, bit);
  gpioWrite(hm.p2_b2, bit);
}

int main(int argc, char* argv[]) {
  atexit(gpioTerminate);
  if (gpioInitialise() < 0) {
    err(1, "initializing");
  }
  uint32_t max_led = 64;
  if (argc > 1) {
    max_led = atoi(argv[1]) * 64;
  }
  gpioSetMode(hm.output_enable, PI_OUTPUT);
  gpioSetMode(hm.clock, PI_OUTPUT);
  gpioSetMode(hm.strobe, PI_OUTPUT);
  gpioSetMode(hm.a, PI_OUTPUT);
  gpioSetMode(hm.b, PI_OUTPUT);
  gpioSetMode(hm.c, PI_OUTPUT);
  gpioSetMode(hm.d, PI_OUTPUT);
  gpioSetMode(hm.e, PI_OUTPUT);
  gpioSetMode(hm.p0_r1, PI_OUTPUT);
  gpioSetMode(hm.p0_g1, PI_OUTPUT);
  gpioSetMode(hm.p0_b1, PI_OUTPUT);
  gpioSetMode(hm.p0_r2, PI_OUTPUT);
  gpioSetMode(hm.p0_g2, PI_OUTPUT);
  gpioSetMode(hm.p0_b2, PI_OUTPUT);
  gpioSetMode(hm.p1_r1, PI_OUTPUT);
  gpioSetMode(hm.p1_g1, PI_OUTPUT);
  gpioSetMode(hm.p1_b1, PI_OUTPUT);
  gpioSetMode(hm.p1_r2, PI_OUTPUT);
  gpioSetMode(hm.p1_g2, PI_OUTPUT);
  gpioSetMode(hm.p1_b2, PI_OUTPUT);
  gpioSetMode(hm.p2_r1, PI_OUTPUT);
  gpioSetMode(hm.p2_g1, PI_OUTPUT);
  gpioSetMode(hm.p2_b1, PI_OUTPUT);
  gpioSetMode(hm.p2_r2, PI_OUTPUT);
  gpioSetMode(hm.p2_g2, PI_OUTPUT);
  gpioSetMode(hm.p2_b2, PI_OUTPUT);

  // Send Data to control register 11
  gpioWrite(hm.clock, LO);
  gpioWrite(hm.output_enable, LO); // Display reset
  gpioWrite(hm.strobe, LO); // ???
  gpioWrite(hm.a, HI);
  gpioWrite(hm.b, LO);
  gpioWrite(hm.c, LO);
  gpioWrite(hm.d, LO);
  gpioWrite(hm.e, LO);

  for (int l = 0; l < max_led; ++l) {
    hmset(kReg2[l % 16]);;
    gpioWrite(hm.clock, HI);
    gpioWrite(hm.clock, LO);
    if (l >= max_led - 12) {
      gpioWrite(hm.strobe, HI);
    } else {
      gpioWrite(hm.strobe, LO);
    }
  }
  gpioWrite(hm.strobe, LO);

  for (int l = 0; l < max_led; ++l) {
    hmset(kReg2[l % 16]);;
    gpioWrite(hm.clock, HI);
    gpioWrite(hm.clock, LO);
    if (l >= max_led - 13) {
      gpioWrite(hm.strobe, HI);
    } else {
      gpioWrite(hm.strobe, LO);
    }
  }
  gpioWrite(hm.strobe, LO);
}

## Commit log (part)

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2025-10-18 Fix dark album rows
2025-10-18 Fix overlapping artist name
2025-10-18 More real time song data
2025-10-18 More compact spacing
2025-10-18 Text wrap around
2025-10-18 Smaller text buffer and scroll hiccup fix
2025-10-18 Background thread for spotify requests
2025-10-18 Delay before scrolling
2025-10-18 Shorter wraparound spacing
2025-10-18 Shorter wraparound spacing for album
2025-10-18 Simple clock
2025-10-18 Fix font path again
2025-10-18 clock fixes
2025-10-18 Cleaner look
2025-10-18 Accurate time and all on one line
2025-10-18 Include day and date
2025-10-18 Reformat
2025-10-18 Another timezone fix and better formatting
2025-10-18 Formatting again
2025-10-18 Alignment
2025-10-18 Alignment again
2025-10-18 Font size
2025-10-18 Dynamic centering
2025-10-18 Weather display first pass
2025-10-18 Rapid updates
2025-10-18 Remove threading for better perf
2025-10-18 Perf
2025-10-19 Weather display updates
2025-10-19 Update spotify faster
2025-10-19 Faster updates
2025-10-19 Weather reformat
2025-10-19 Icon debugging
2025-10-19 Icon enhancements
2025-10-19 Move high temp down
2025-10-19 Reformatting
2025-10-19 Resize time
2025-10-19 New font
2025-10-19 Cmd line locale config
2025-10-19 Tattoo test
2025-10-19 Tattoo another pass
2025-10-19 Remove tattoo time
2025-10-19 Remove background
2025-10-19 Default values
2025-10-19 Stock tracker first pass
2025-10-19 Env key
2025-10-19 Env ignore
2025-10-19 Debug
2025-10-19 Font fix
2025-10-19 Font fix again
2025-10-19 Back to advanced
2025-10-19 Yahoo API
2025-10-19 Fix timing of display
2025-10-19 Test
2025-10-19 Simple case
2025-10-19 Smaller font and 2px padding
2025-10-19 Change values
2025-10-19 Right align
2025-10-19 Chart
2025-10-19 Chart fix
2025-10-19 Disable chart, debug
2025-10-19 Debug and historical data
2025-10-19 Debug and historical data again
2025-10-19 Fix deadlock
2025-10-19 Timeout issue
2025-10-19 64 days of history
2025-10-19 Chart infill
2025-10-19 Dynamically include trending stocks
2025-10-19 Smoother scrolling
2025-10-19 Threading to help with scroll lag
2025-10-19 Scroll slower
2025-10-19 Longer static text before scroll, quicker data refresh
2025-10-19 Fix chart blinking
2025-10-19 Blinking fix
2025-10-19 Chart disappear fix
2025-10-19 Chart debug
2025-10-19 Gif viewer
2025-10-19 Add url param for gif
2025-10-19 Fit gif to screen
2025-10-19 Fit by default
2025-10-19 Video player
2025-10-19 Video url
2025-10-19 Perf improvements
2025-10-20 Add weather icon mapping system and configuration files
    - Add map_weather_icons.py script for processing weather icons
    - Add .gitignore for assets directory
    - Add .gitattributes configuration
2025-10-20 Add processed weather icons for LED display
    - 18 weather icons optimized for 32x32 LED matrix
    - All OpenWeatherMap icon codes covered (01d-50n)
    - Icons resized and color-optimized for LED display visibility
2025-10-20 Add basic weather icons: Sun, Moon, and Stars
    - Add various sun icons (clear day conditions)
    - Add moon and star icons (clear night conditions)
    - High-quality source assets for weather icon mapping
2025-10-20 Reisze icons
2025-10-20 Alt sun
2025-10-20 Improve weather display layout: smaller city font and better time positioning
    - Add tiny 4x6 font for more compact city name display
    - Move time display to Y=5 for better clearance from 26x26 weather icons
    - Use tiny font for city name to reduce visual clutter
2025-10-20 Resize
2025-10-20 Reposition
2025-10-20 Overwrite icon
2025-10-20 Debug borders
2025-10-20 Draw time after icon
2025-10-20 Darken dull pixels
2025-10-20 Resize icon
2025-10-20 Rework images
2025-10-20 Dim pixel fix
2025-10-20 Center tmps
2025-10-20 Tests and readme
2025-10-20 Screen touchups
2025-10-20 Remove unnecessary extra info
2025-10-20 Param for time
2025-10-20 Param for time fix
2025-10-20 Lighter grey progress bar
2025-10-20 Status indicator
2025-10-20 Icon fixes
2025-10-20 Done font
2025-10-20 Subtitle
2025-10-20 Whitespace
2025-10-22 Fix imports
2025-10-22 Move remaining apps
2025-10-22 Consolidate shared functionality
2025-10-22 Refactor base matrix class:
2025-10-22 Fix font references
2025-10-22 Retro clock
2025-10-22 Change style of retro clock
2025-10-22 Background color and digit windows
2025-10-22 Brightness setting
2025-10-22 Stock display updates
2025-10-22 Color reference updates in stocks
2025-10-22 Small style tweaks
2025-10-22 Color update
2025-10-22 Time change animation
2025-10-22 Missing config
2025-10-22 Flip animation changes
2025-10-22 Flip animation update again
2025-10-22 Another go at the flip animation
2025-10-22 Brightness settings
2025-10-22 Remove traces of deprecated stock tracker
2025-10-22 Rename advanced-stock-tracker
2025-10-22 Fix stock display
2025-10-22 Right align text
2025-10-22 Right align text fix
2025-10-22 Font fixes
2025-10-23 Font fixes again please work
2025-10-23 Font fixes again please work pt 2
2025-10-23 Position updates
2025-10-23 Make chart bigger
2025-10-23 Comments
2025-10-23 Revert to simple time update
2025-10-23 Timezone support
2025-10-23 DRY timezone
2025-10-23 Timezone manager again
2025-10-23 Default to denver timezone
2025-10-23 Cleanup
2025-10-23 Timezone fix for real
2025-10-23 UTC-6 instead of -7
2025-10-25 Write a wrapper for Pillow.Image.getim()
2025-10-25 refactor on hardware
2025-10-25 Update removed ANTIALIAS constant to LANCZOS
2025-10-27 Refactor broken unsafe SetImagePillow()
2025-10-27 Remove extra pointer indirection
2025-10-27 remove unused var
2025-10-30 New DoubleZ multiplexer. Used for 64x32 HUB75 RGB with ICN2037BP chip.
2025-11-08 New DoubleZ multiplexer. Used for 64x32 HUB75 RGB with ICN2037BP chip. (#1819)
2025-11-26 Update README.md
    Fix
    https://github.com/hzeller/rpi-rgb-led-matrix/issues/1825
2025-11-27 Fix memory leak for color lookup (#1763)
    * add singleton lookup table
    * move method and change return type
    * make luminance_cie1931 private
2025-11-27 Reuse CreateFrameCanvas() in samples/gif-viewer.py
2025-11-27 Change thumbnail filter from ANTIALIAS to LANCZOS
2025-11-27 Update README.md on python support
2025-11-27 added link to https://www.acmesystems.it/HAT-A3
    replaces https://github.com/hzeller/rpi-rgb-led-matrix/pull/777
2025-11-27 Update README.md
    Mention https://github.com/hzeller/rpi-rgb-led-matrix/pull/1478/files until @ledvinap can give better documentation.
2025-11-27 show custom mapper
    fixes https://github.com/hzeller/rpi-rgb-led-matrix/issues/1732
2025-11-27 new issue template
2025-11-27 scripts to handle bugs
2025-11-27 files on how to handle bugs
2025-11-27 Rename README to .README
2025-11-28 Update runtext.py with more parameters
2025-12-02 chore: push local updates
2025-12-04 Upgrade TargetFramework to .NET 8.0
2025-12-09 Remove distutils over setuptools
2025-12-10 Add notes on parameters for streams
2025-12-10 Attempt to fix emoji in wiring.md
2025-12-10 Check to see if space really affected it
2025-12-11 Unify examples config
2025-12-11 Adding Interfaces
2025-12-11 Adding interface files
2025-12-11 Update README.md
    Python fork header mistakenly included, now removed.
    Basic information on installing Python bindings included under Python Support section.
2025-12-15 Add StackToRow mapper implementation (#1)
    * Add initial windmill mapper
    * Add new windmill
    * Add nearly working windmill
    * Slight fix
    * Fix x axis
    * Add working mapper
2025-12-16 Add example layout
2025-12-16 Ignore Visual Studio files
2025-12-16 Add powershell script to sync files with pi and build
2025-12-18 Add Visual Studio folder to gitignore
2025-12-18 Add sync script
2025-12-18 Add UID logging, allow passing filename as cmdline param
2025-12-19 Simplify filename prompt
2025-12-19 Declare options once, at start of program
2025-12-20 Set --led-no-drop-privs in Bindings
2025-12-22 Add additional multiplexing types to enum
2026-01-03 Set up tooling
2026-01-03 Revert "Add sync script"
    This reverts commit 40c4147ab6659039d7056fc17e5682d782070354.
2026-01-03 Minor README edit
2026-01-03 Make content-streamer functions externally accessible
2026-01-04 Add StreamReaderWrapper
2026-01-04 expose canvas field
2026-01-04 Update bindings to use lowercase_with_underscores. Fix cc file. Pass privs option. WORKING!!
2026-01-04 RenameStreamReaderWrapper to ContentStreamer
2026-01-04 Initial example
2026-01-04 Publish task targets specific csproj
2026-01-04 Ignore sln files (It will be auto-generated anyway)
2026-01-04 Tidy example
2026-01-04 Implement MatrixOptions.cs - all examples use same options
2026-01-04 Add CheckFileHeader to check if file is a valid stream
2026-01-04 Add ClearCanvas
2026-01-04 Revert out exposing ReadFileHeader - pointless as you need to new up a StreamReader to call it, by which point an exception would have been thrown if it was invalid
2026-01-04 Move MatrixOptions into examples folder
2026-01-04 Add instructions for Font example
2026-01-04 Add instructions for StreamPlayer
2026-01-04 Exclude example files from bindings project, not whole folder
2026-01-04 Remove redundant CheckFileHeader
2026-01-04 Move Clear from Content Streamer to Canvas, as it logically belongs there
2026-01-04 Expose required methods from API and create C# bindings for content-streamer
2026-01-04 Implement example using c# ContentStreamer
2026-01-04 Add tooling
2026-01-04 Change exclusions
2026-01-05 Remove redundant binding to clear
2026-01-05 Change holdTimeUs from ref to out
2026-01-07 Remove MatrixOptions
2026-01-07 Remove superfluous ImageSharp reference
2026-01-08 initial attempt, open not happy
2026-01-08 Fix issue with open
2026-01-08 Revert needlessly modified files back
2026-01-09 Simplify member access, remove redundant assignment
2026-01-10 Add IsCompatible to content-streamer
2026-01-11 Compiler optimization (Native CPU arch compile params)
2026-01-11 Throw ObjectDisposedException if StreamIO is not initialized
2026-01-12 Fixed random warning messages during build step
2026-01-12 Fix warning on build
2026-01-13 Add VSCode tasks for cross-compilation for windows
2026-01-15 Added a central bash runner script to improve flickering
2026-01-24 Changes made in response to comments. Removed interfaces for now as need further discussion
2026-01-27 Trying scikit-build-core.
2026-01-27 In-progress scikit-build-core progress. It's getting close....
2026-01-27 Add support for Raspberry Pi CM4S model
2026-02-10 video-viewer: make compile in modern times.
2026-02-10 Modernize led-image-viewer random shuffle use.
2026-02-10 Make it possible to choose compiler environment.
2026-02-10 Configure lto and march options at a central place.
    config.mk contains what is necessary (things are dependent on
    compiler, so make it simple to deal with it once)
2026-02-10 PixelDesignatorMap: use std::vector instead of raw buffer.
2026-02-10 Squash warning about ignoring write() return value.
2026-02-10 Now that we distinguish compilers, set lto to 2 again.
2026-03-06 Remove the Python make checks from Github CI.
2026-03-06 Remove python from make clean.
2026-03-17 Added RT Kernel
    FIX: https://github.com/hzeller/rpi-rgb-led-matrix/issues/1754
2026-03-17 Update README.md to point to RT kernel documentation
    Fix https://github.com/hzeller/rpi-rgb-led-matrix/issues/1754
2026-03-23 Revert C# readme to original state
2026-03-24 Real Time Kernel Documentation Update
2026-03-27 Fix warning: cc1plus: warning: ‘-Werror=’ argument ‘-Werror=implicit-function-declaration’ is not valid for C++
2026-03-31 Added MeasureText function
2026-03-31 RT Kernel Documentation Update - Pi 3 / Zero 2W guide steps.
2026-04-05 Added adafruit active-3 board
2026-04-05 Modify Python installation commands in README
    Updated Python installation instructions in README.
2026-04-07 Update InternalRGBLedMatrixOptions.cs
    Fix https://github.com/hzeller/rpi-rgb-led-matrix/issues/1867
2026-04-25 Raspberry Pi5 Support v0.06
